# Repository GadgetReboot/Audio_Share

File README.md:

# Audio_Share
<br><br><BR><BR>
Take one stereo audio line input and share to 3 line outputs with level adjust

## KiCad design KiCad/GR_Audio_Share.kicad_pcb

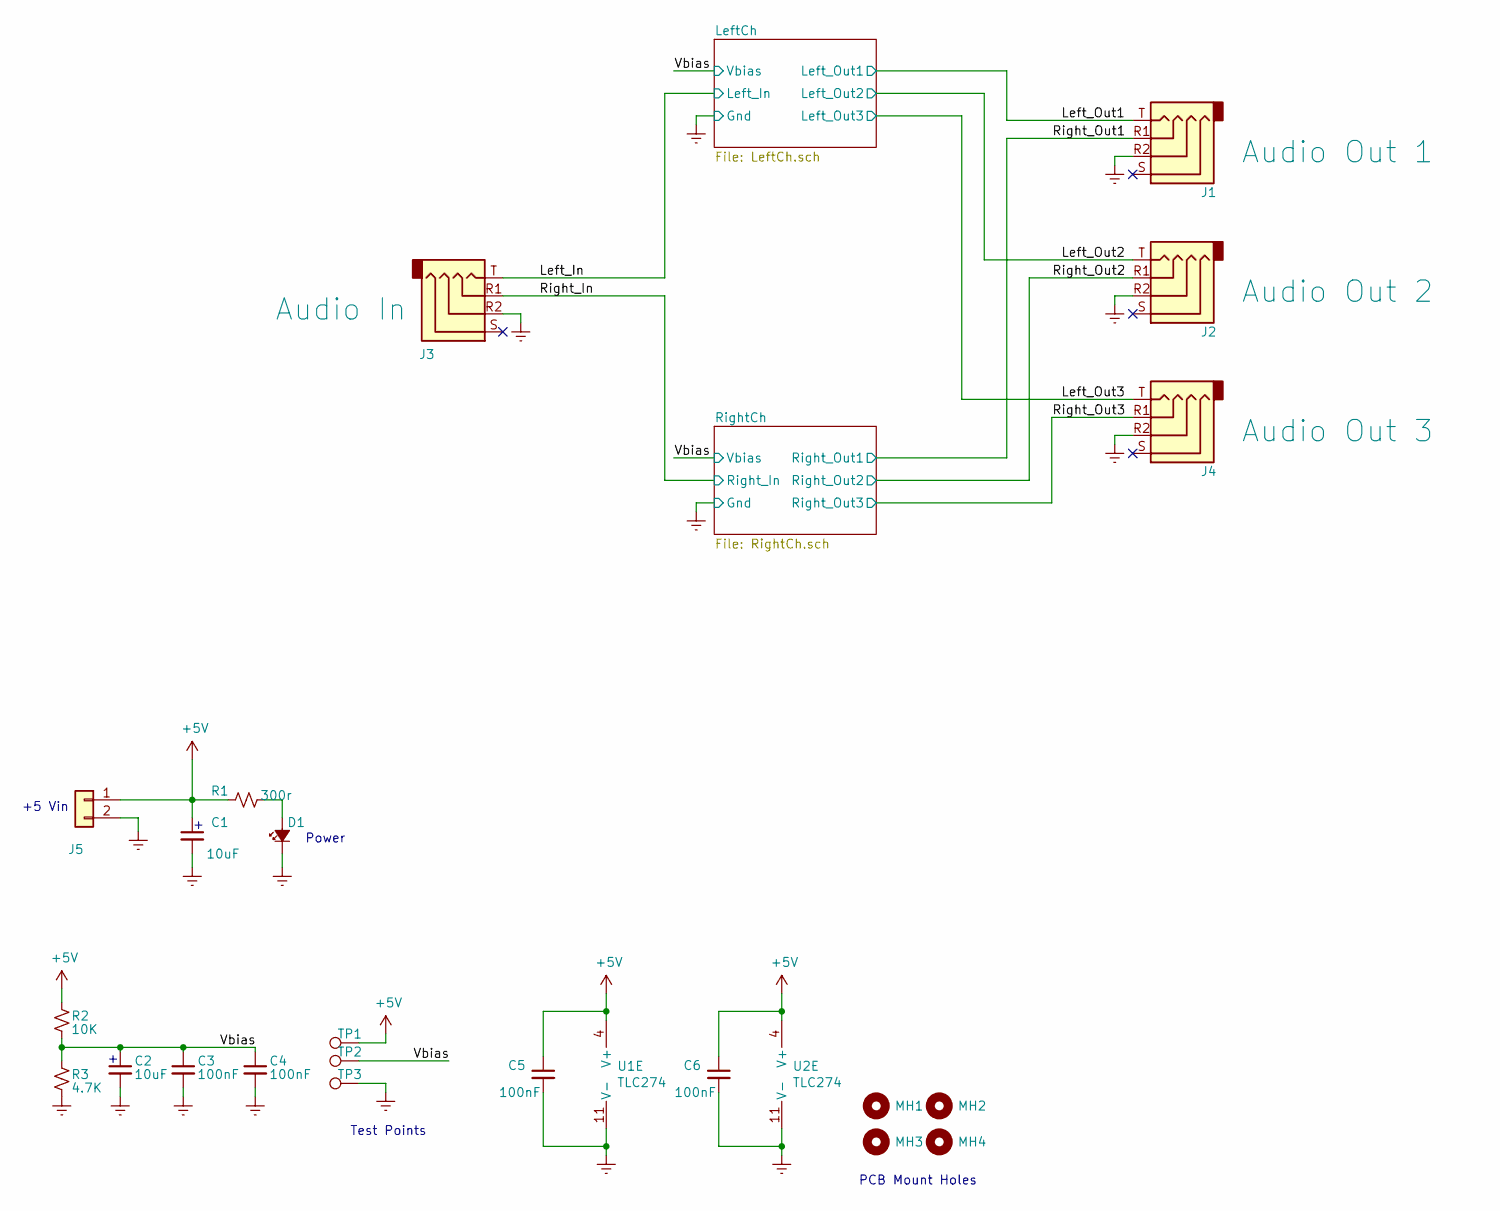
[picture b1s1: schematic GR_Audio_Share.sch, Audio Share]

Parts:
C1, C2: 10uF; CP_Radial_D5.0mm_P2.50mm
C3, C4, C5, C6: 100nF; C_Disc_D3.0mm_W2.0mm_P2.50mm
D1: LED_Small_ALT; LED_D5.0mm
J1: Audio Out 1; PJ320A
J2: Audio Out 2; PJ320A
J3: Audio In; PJ320A
J4: Audio Out 3; PJ320A
J5: Conn_01x02; PinHeader_1x02_P2.54mm_Vertical
MH1, MH2, MH3, MH4: MountingHole; MountingHole_3.2mm_M3
R1: 300r; R_Axial_DIN0204_L3.6mm_D1.6mm_P7.62mm_Horizontal
R2: 10K; R_Axial_DIN0204_L3.6mm_D1.6mm_P7.62mm_Horizontal
R3: 4.7K; R_Axial_DIN0204_L3.6mm_D1.6mm_P7.62mm_Horizontal
TP1, TP2, TP3: TestPoint; TestPoint_Loop_D1.80mm_Drill1.0mm_Beaded
U1, U2: TLC274; DIP-14_W7.62mm_Socket_LongPads

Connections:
+5V: C1.1, C5.1, C6.1, J5.1, R1.1, R2.2, TP1.1, U1.4 (V+), U2.4 (V+)
/Left_In: J3.T; also elsewhere on the board
/Left_Out1: J1.T; also elsewhere on the board
/Left_Out2: J2.T; also elsewhere on the board
/Left_Out3: J4.T; also elsewhere on the board
/Right_In: J3.R1; also elsewhere on the board
/Right_Out1: J1.R1; also elsewhere on the board
/Right_Out2: J2.R1; also elsewhere on the board
/Right_Out3: J4.R1; also elsewhere on the board
/Vbias: C2.1, C3.1, C4.1, R2.1, R3.2, TP2.1; also elsewhere on the board
GNDREF: C1.2, C2.2, C3.2, C4.2, C5.2, C6.2, D1.1 (K), J1.R2, J2.R2, J3.R2, J4.R2, J5.2, R3.1, TP3.1, U1.11 (V-), U2.11 (V-)
unnamed: D1.2 (A), R1.2

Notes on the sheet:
+5 Vin
PCB Mount Holes
Test Points
Power

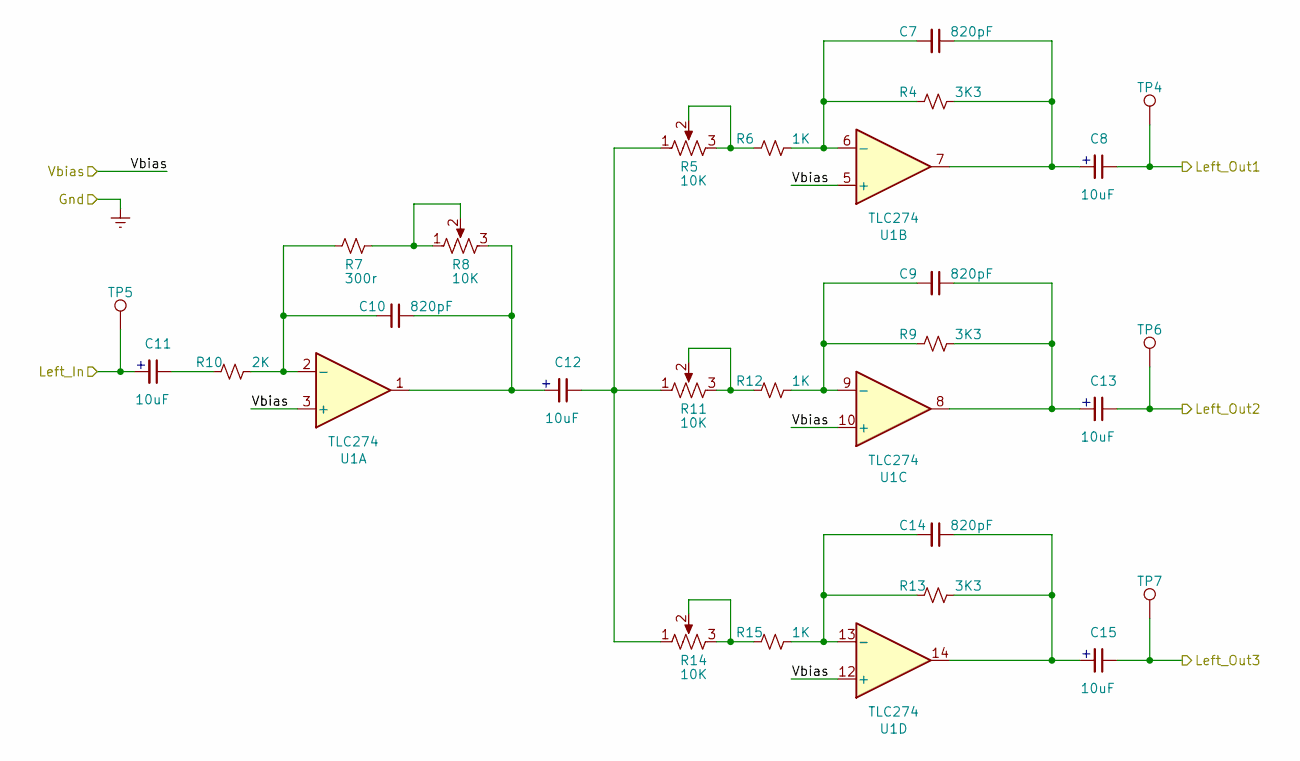
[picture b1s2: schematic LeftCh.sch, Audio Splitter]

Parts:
C7, C9, C10, C14: 820pF; C_Disc_D3.0mm_W2.0mm_P2.50mm
C8, C11, C12, C13, C15: 10uF; CP_Radial_D5.0mm_P2.50mm
R4, R9, R13: 3K3; R_Axial_DIN0204_L3.6mm_D1.6mm_P7.62mm_Horizontal
R5, R8, R11, R14: 10K; Potentiometer_Vishay_T73YP_Vertical
R6, R12, R15: 1K; R_Axial_DIN0204_L3.6mm_D1.6mm_P7.62mm_Horizontal
R7: 300r; R_Axial_DIN0204_L3.6mm_D1.6mm_P7.62mm_Horizontal
R10: 2K; R_Axial_DIN0204_L3.6mm_D1.6mm_P7.62mm_Horizontal
TP4, TP5, TP6, TP7: TestPoint; TestPoint_Loop_D1.80mm_Drill1.0mm_Beaded
U1: TLC274; DIP-14_W7.62mm_Socket_LongPads

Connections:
/Left_In: C11.2, TP5.1; also elsewhere on the board
/Left_Out1: C8.1, TP4.1; also elsewhere on the board
/Left_Out2: C13.1, TP6.1; also elsewhere on the board
/Left_Out3: C15.1, TP7.1; also elsewhere on the board
/Vbias: U1.3 (+), U1.5 (+), U1.10 (+), U1.12 (+); also elsewhere on the board
unnamed: C7.1, C8.2, R4.2, U1.7
unnamed: C7.2, R4.1, R6.2, U1.6 (-)
unnamed: C9.2, R9.1, R12.2, U1.9 (-)
unnamed: C10.1, C12.2, R8.3, U1.1
unnamed: C10.2, R7.1, R10.2, U1.2 (-)
unnamed: C11.1, R10.1
unnamed: C12.1, R5.1, R11.1, R14.1
unnamed: C9.1, C13.2, R9.2, U1.8
unnamed: C14.1, C15.2, R13.2, U1.14
unnamed: C14.2, R13.1, R15.2, U1.13 (-)
unnamed: R5.2, R5.3, R6.1
unnamed: R7.2, R8.1, R8.2
unnamed: R11.2, R11.3, R12.1
unnamed: R14.2, R14.3, R15.1

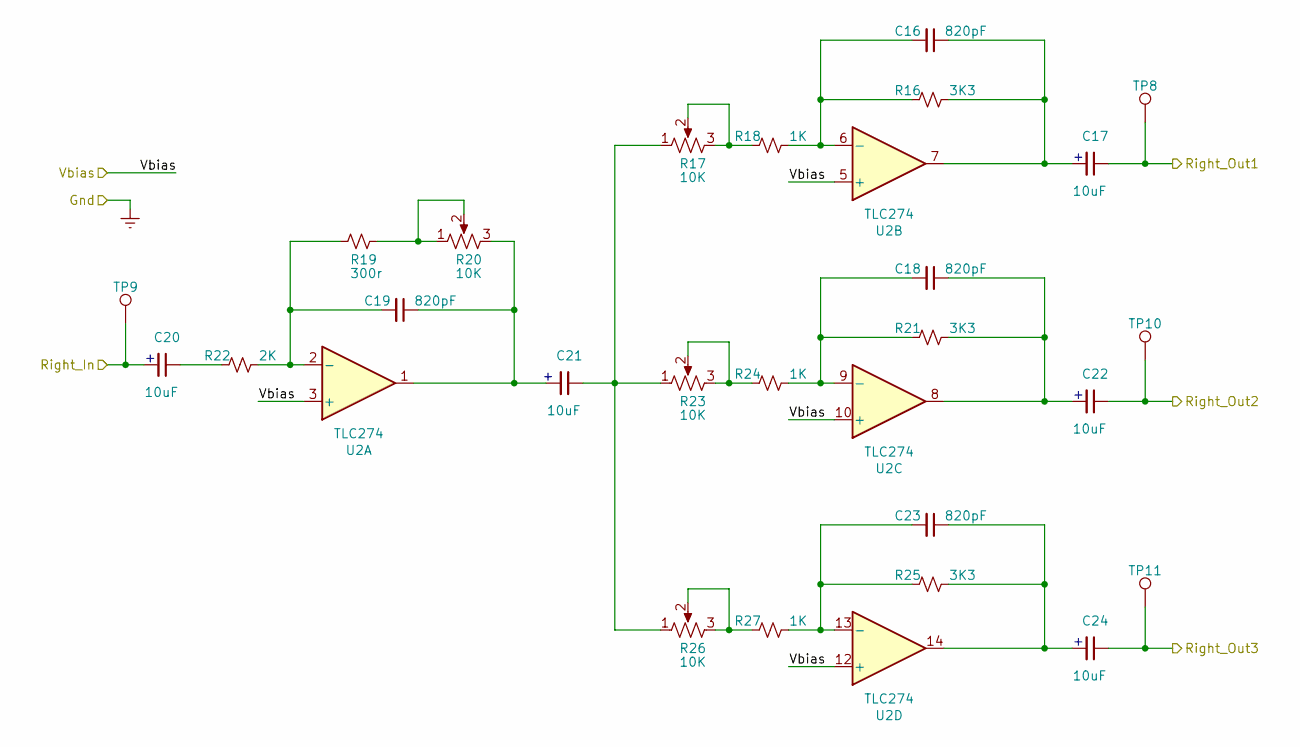
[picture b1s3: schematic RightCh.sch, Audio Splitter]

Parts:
C16, C18, C19, C23: 820pF; C_Disc_D3.0mm_W2.0mm_P2.50mm
C17, C20, C21, C22, C24: 10uF; CP_Radial_D5.0mm_P2.50mm
R16, R21, R25: 3K3; R_Axial_DIN0204_L3.6mm_D1.6mm_P7.62mm_Horizontal
R17, R20, R23, R26: 10K; Potentiometer_Vishay_T73YP_Vertical
R18, R24, R27: 1K; R_Axial_DIN0204_L3.6mm_D1.6mm_P7.62mm_Horizontal
R19: 300r; R_Axial_DIN0204_L3.6mm_D1.6mm_P7.62mm_Horizontal
R22: 2K; R_Axial_DIN0204_L3.6mm_D1.6mm_P7.62mm_Horizontal
TP8, TP9, TP10, TP11: TestPoint; TestPoint_Loop_D1.80mm_Drill1.0mm_Beaded
U2: TLC274; DIP-14_W7.62mm_Socket_LongPads

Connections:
/Right_In: C20.2, TP9.1; also elsewhere on the board
/Right_Out1: C17.1, TP8.1; also elsewhere on the board
/Right_Out2: C22.1, TP10.1; also elsewhere on the board
/Right_Out3: C24.1, TP11.1; also elsewhere on the board
/Vbias: U2.3 (+), U2.5 (+), U2.10 (+), U2.12 (+); also elsewhere on the board
unnamed: C16.1, C17.2, R16.2, U2.7
unnamed: C16.2, R16.1, R18.2, U2.6 (-)
unnamed: C18.1, C22.2, R21.2, U2.8
unnamed: C18.2, R21.1, R24.2, U2.9 (-)
unnamed: C19.1, C21.2, R20.3, U2.1
unnamed: C19.2, R19.1, R22.2, U2.2 (-)
unnamed: C20.1, R22.1
unnamed: C21.1, R17.1, R23.1, R26.1
unnamed: C23.1, C24.2, R25.2, U2.14
unnamed: C23.2, R25.1, R27.2, U2.13 (-)
unnamed: R17.2, R17.3, R18.1
unnamed: R19.2, R20.1, R20.2
unnamed: R23.2, R23.3, R24.1
unnamed: R26.2, R26.3, R27.1

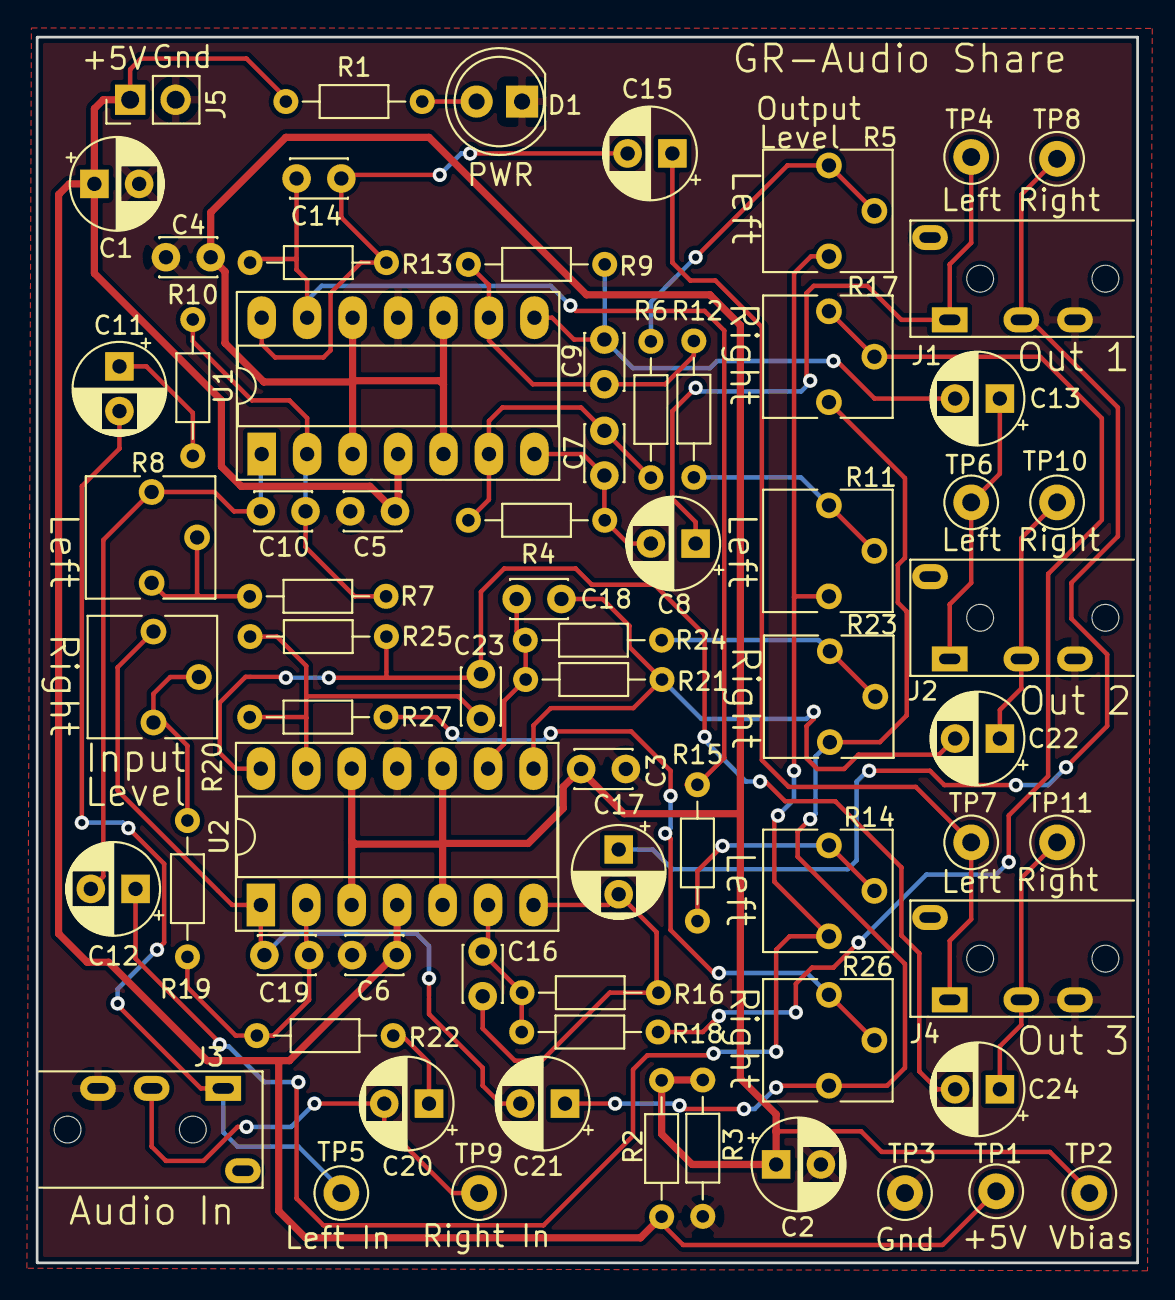
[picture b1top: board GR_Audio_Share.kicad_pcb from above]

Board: 2 copper layers, 61.5 x 68.5 mm, 70 parts (0 on the bottom side), 40 nets.
